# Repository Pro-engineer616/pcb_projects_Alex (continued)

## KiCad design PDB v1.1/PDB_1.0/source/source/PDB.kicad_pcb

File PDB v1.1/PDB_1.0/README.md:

PDB (Power delivery board Rev. 1.0)

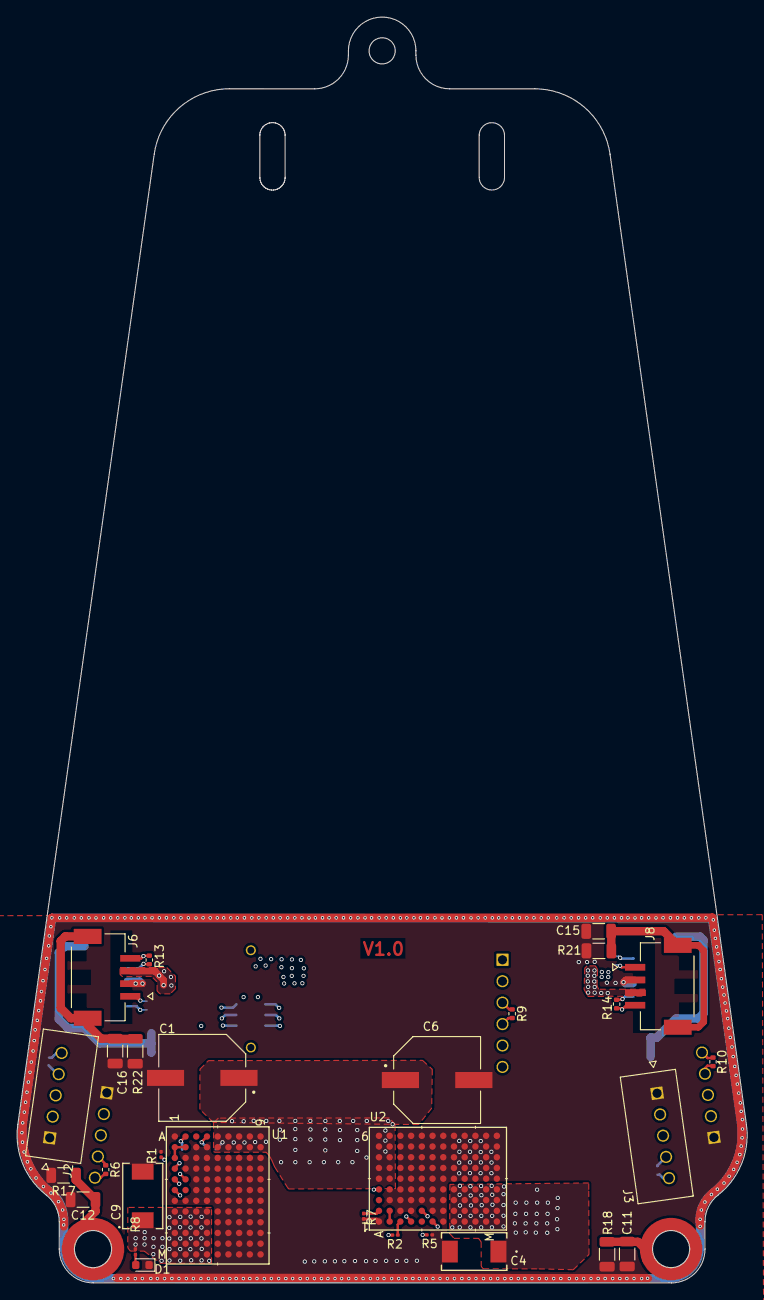
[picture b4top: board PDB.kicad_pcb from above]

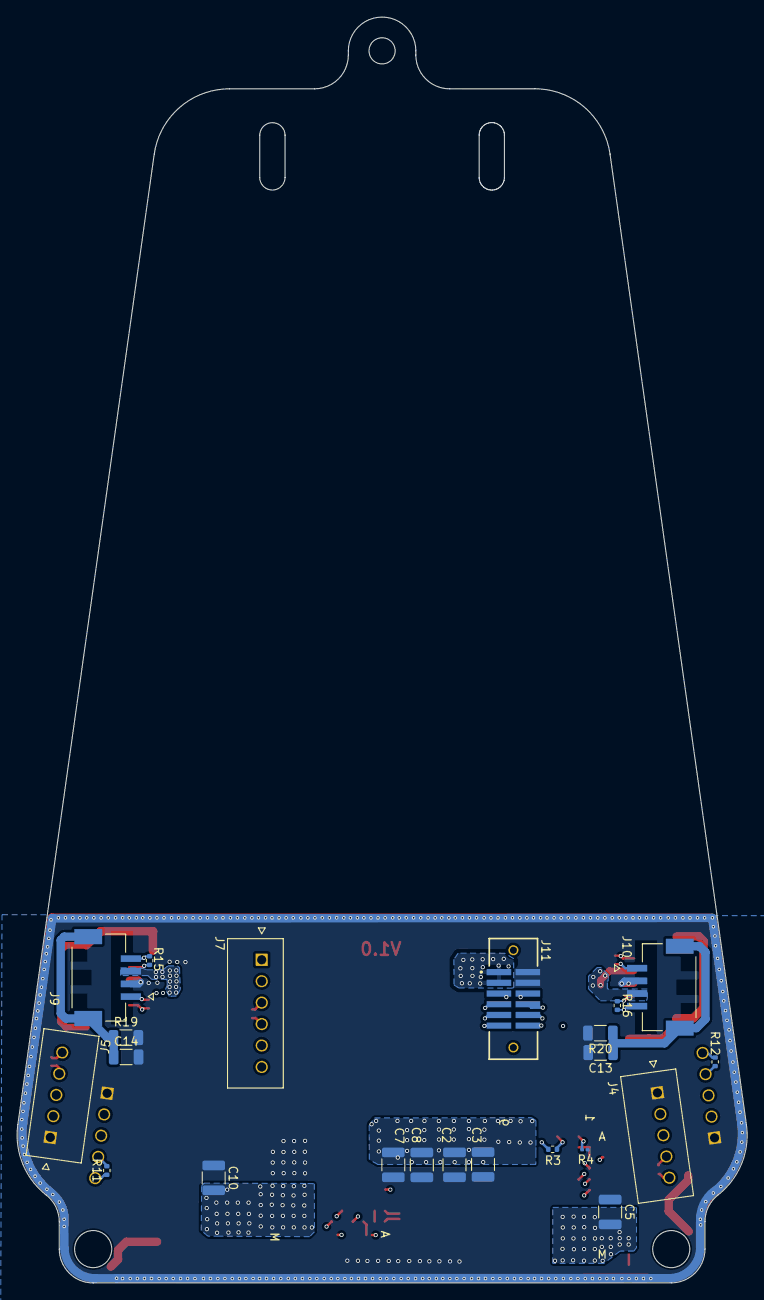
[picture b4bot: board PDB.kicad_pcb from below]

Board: 4 copper layers, 86.5 x 150.0 mm, 53 parts (22 on the bottom side), 29 nets.

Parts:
C1, C6: 15uf; CAP_100SXV15MX
C2, C3, C7, C8: 10u; C_1210_3225Metric
C4, C9: 150uF; CAP_TRM-E-2917_AVX-L
C5, C10: 100uF; C_1210_3225Metric
C11, C12, C13, C14, C15, C16: 470pF; C_1206_3216Metric
D1: NCD0603C1; LED_0603_1608Metric
J2, J3, J4, J5: 1719710105; MOLEX_1719710105
J6, J8, J9, J10: 2132250430; MOLEX_2132250430
J7: 1719710106; MOLEX_1719710106
J11: TFM-106-02-L-D-WT; SAMTEC_TFM-106-02-L-D-WT
MP1, MP2: WA-SMSI_9774XXX360; WA-SMSI_9774120360
R1, R5: 124k; R_0201_0603Metric
R2: 100k; R_0201_0603Metric
R3: 374k; R_0402_1005Metric
R4, R7: 2.87k; R_0201_0603Metric
R6, R9, R10, R11, R12, R13, R14, R15, R16: 120R; R_0402_1005Metric
R8: 10k; R_0201_0603Metric
R17, R18, R19, R20, R21, R22: 2M; C_1206_3216Metric
U1, U2: LTM8064IY#PBF; BGA108_16X11P9_ADI

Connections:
+8V: C4.1, C5.2, C9.1, C10.2, J2.2, J3.2, J4.2, J5.2, J7.5, R8.2, U1.H1 (VOUT), U1.H2 (VOUT), U1.H3 (VOUT), U1.H4 (VOUT), U1.J1 (VOUT), U1.J2 (VOUT), U1.J3 (VOUT), U1.J4 (VOUT), U1.K1 (VOUT), U1.K2 (VOUT), U1.K3 (VOUT), U1.K4 (VOUT), U1.L1 (VOUT), U1.L2 (VOUT), U1.L3 (VOUT), U1.L4 (VOUT), U1.M1 (VOUT), U1.M2 (VOUT), U1.M3 (VOUT), U1.M4 (VOUT), U2.H1 (VOUT), U2.H2 (VOUT), U2.H3 (VOUT), U2.H4 (VOUT), U2.J1 (VOUT), U2.J2 (VOUT), U2.J3 (VOUT), U2.J4 (VOUT), U2.K1 (VOUT), U2.K2 (VOUT), U2.K3 (VOUT), U2.K4 (VOUT), U2.L1 (VOUT), U2.L2 (VOUT), U2.L3 (VOUT), U2.L4 (VOUT), U2.M1 (VOUT), U2.M2 (VOUT), U2.M3 (VOUT), U2.M4 (VOUT)
/power/IOUTMON: R2.1, U2.C1 (CTRL1)
/power/PWR_RUN: R3.1, U1.A4 (RUN), U2.A4 (RUN)
/power/PWR_SS: U1.D1 (SS), U2.D1 (SS)
/power/SYNC: U1.F1 (SYNC), U2.F1 (SYNC)
CAN H1: J2.5, J3.5, J4.5, J5.5, J6.1, J7.3, J8.1, J9.1, J10.1, J11.05, R6.1, R9.1, R10.1, R11.1, R12.1, R13.1, R14.1, R15.1, R16.1
CAN L1: J2.4, J3.4, J4.4, J5.4, J6.4, J7.4, J8.4, J9.4, J10.4, J11.06, R6.2, R9.2, R10.2, R11.2, R12.2, R13.2, R14.2, R15.2, R16.2
Detach: J7.2, J11.07
GND: C1.2, C2.2, C3.2, C4.2, C5.1, C6.2, C7.2, C8.2, C9.2, C10.1, C11.2, C12.2, C13.2, C14.2, C15.2, C16.2, D1.1 (K), J2.1, J3.1, J4.1, J5.1, J6.2, J8.2, J9.2, J10.2, J11.02, J11.04, R1.1, R4.2, R5.1, R7.2, R17.2, R18.2, R19.2, R20.2, R21.2, R22.2, U1.A1 (GND), U1.B3 (GND), U1.B4 (GND), U1.C2 (GND), U1.C3 (GND), U1.C4 (GND), U1.C5 (GND), U1.C6 (GND), U1.C7 (GND), U1.C8 (GND), U1.C9 (GND), U1.D2 (GND), U1.D3 (GND), U1.D4 (GND), U1.D5 (GND), U1.D6 (GND), U1.D7 (GND), U1.D8 (GND), U1.D9 (GND), U1.E3 (GND), U1.E4 (GND), U1.E5 (GND), U1.E6 (GND), U1.E7 (GND), U1.E8 (GND), U1.E9 (GND), U1.F3 (GND), U1.F4 (GND), U1.F5 (GND), U1.F6 (GND), U1.F7 (GND), U1.F8 (GND), U1.F9 (GND), U1.G1 (GND), U1.G2 (GND), U1.G3 (GND), U1.G4 (GND), U1.G5 (GND), U1.G6 (GND), U1.G7 (GND), U1.G8 (GND), U1.G9 (GND), U1.H5 (GND), U1.H6 (GND), U1.H7 (GND), U1.H8 (GND), U1.H9 (GND), U1.J5 (GND), U1.J6 (GND), U1.J7 (GND), U1.J8 (GND), U1.J9 (GND), U1.K5 (GND), U1.K6 (GND), U1.K7 (GND), U1.K8 (GND), U1.K9 (GND), U1.L5 (GND), U1.L6 (GND), U1.L7 (GND), U1.L8 (GND), U1.L9 (GND), U1.M5 (GND), U1.M6 (GND), U1.M7 (GND), U1.M8 (GND), U1.M9 (GND), U2.A1 (GND), U2.B3 (GND), U2.B4 (GND), U2.C2 (GND), U2.C3 (GND), U2.C4 (GND), U2.C5 (GND), U2.C6 (GND), U2.C7 (GND), U2.C8 (GND), U2.C9 (GND), U2.D2 (GND), U2.D3 (GND), U2.D4 (GND), U2.D5 (GND), U2.D6 (GND), U2.D7 (GND), U2.D8 (GND), U2.D9 (GND), U2.E3 (GND), U2.E4 (GND), U2.E5 (GND), U2.E6 (GND), U2.E7 (GND), U2.E8 (GND), U2.E9 (GND), U2.F2 (MODE), U2.F3 (GND), U2.F4 (GND), U2.F5 (GND), U2.F6 (GND), U2.F7 (GND), U2.F8 (GND), U2.F9 (GND), U2.G1 (GND), U2.G2 (GND), U2.G3 (GND), U2.G4 (GND), U2.G5 (GND), U2.G6 (GND), U2.G7 (GND), U2.G8 (GND), U2.G9 (GND), U2.H5 (GND), U2.H6 (GND), U2.H7 (GND), U2.H8 (GND), U2.H9 (GND), U2.J5 (GND), U2.J6 (GND), U2.J7 (GND), U2.J8 (GND), U2.J9 (GND), U2.K5 (GND), U2.K6 (GND), U2.K7 (GND), U2.K8 (GND), U2.K9 (GND), U2.L5 (GND), U2.L6 (GND), U2.L7 (GND), U2.L8 (GND), U2.L9 (GND), U2.M5 (GND), U2.M6 (GND), U2.M7 (GND), U2.M8 (GND), U2.M9 (GND)
GND_FUSE: J7.1, J11.08
unnamed: C11.1, MP2.1, R18.1
unnamed: C12.1, MP1.1, R17.1
unnamed: D1.2 (A), R8.1
unnamed: C16.1, J6.S1 (SHIELD1), J6.S2 (SHIELD2), R22.1
unnamed: C15.1, J8.S1 (SHIELD1), J8.S2 (SHIELD2), R21.1
unnamed: C14.1, J9.S1 (SHIELD1), J9.S2 (SHIELD2), R19.1
unnamed: C13.1, J10.S1 (SHIELD1), J10.S2 (SHIELD2), R20.1
unnamed: U1.B1 (CTRL2), U1.B2 (VREF), U1.C1 (CTRL1)
unnamed: R4.1, U1.A2 (FB)
unnamed: R2.2, U1.E1 (IOUTMON)
unnamed: R1.2, U1.E2 (RT)
unnamed: U2.B1 (CTRL2), U2.B2 (VREF)
unnamed: R7.1, U2.A2 (FB)
unnamed: R5.2, U2.E2 (RT)
PWM1: J5.3, J11.09
PWM2: J4.3, J11.10
PWM3: J3.3, J11.11
PWM4: J2.3, J11.12
VBAT: C1.1, C2.1, C3.1, C6.1, C7.1, C8.1, J6.3, J8.3, J9.3, J10.3, J11.01, J11.03, R3.2, U1.A5 (VIN), U1.A6 (VIN), U1.A7 (VIN), U1.A8 (VIN), U1.A9 (VIN), U1.B5 (VIN), U1.B6 (VIN), U1.B7 (VIN), U1.B8 (VIN), U1.B9 (VIN), U2.A5 (VIN), U2.A6 (VIN), U2.A7 (VIN), U2.A8 (VIN), U2.A9 (VIN), U2.B5 (VIN), U2.B6 (VIN), U2.B7 (VIN), U2.B8 (VIN), U2.B9 (VIN)

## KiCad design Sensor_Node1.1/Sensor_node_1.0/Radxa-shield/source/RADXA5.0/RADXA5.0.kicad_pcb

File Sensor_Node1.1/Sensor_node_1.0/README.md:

View this project on [CADLAB.io](https://cadlab.io/project/28262). 

# sensor_node
Airspeed, Compass and UART as CAN sensor

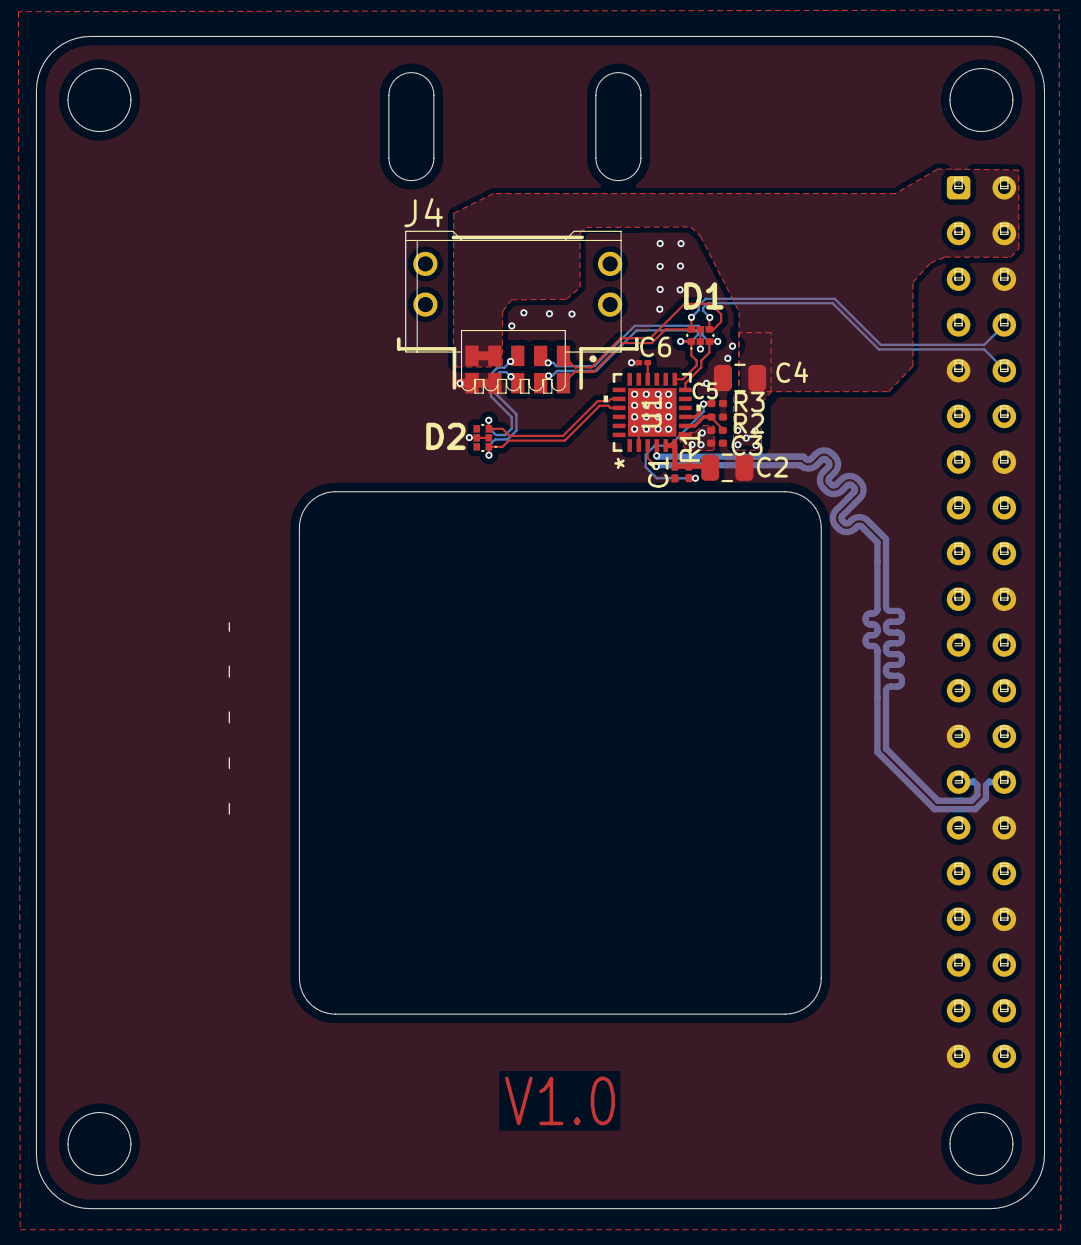
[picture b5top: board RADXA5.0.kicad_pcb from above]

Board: 2 copper layers, 56.0 x 65.1 mm, 14 parts (1 on the bottom side), 14 nets.

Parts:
C1, C3, C5: 100n; C_0201_0603Metric
C2, C4: 10u; C_0805_2012Metric
C6: 4.7u; C_01005_0402Metric
D1, D2: PESD3V3L4UF,115; PESD3V3L5UF115
J1: Conn_02x10_Odd_Even; Samtec_HLE-120-02-xx-DV-TE_2x20_P2.54mm_Horizontal
J4: TFM-105-02-L-DH; SAMTEC_TFM-105-02-L-DH
R1: 4.3k; R_0201_0603Metric
R2: 24k; R_0201_0603Metric
R3: 47k; R_0201_0603Metric
U1: CP2105-F01-GM; QFN24_4X4_SIL-L

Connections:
5VSYS: C3.1, C4.1, J1.2, J1.4, J4.07, J4.09, R2.1, U1.7 (REGIN)
GND: C1.2, C2.2, C3.2, C4.2, C5.2, C6.2, D1.2 (common_anode_1), D1.5 (common_anode_2), D2.2 (common_anode_1), D2.5 (common_anode_2), J1.6, J1.9, J1.14, J1.20, J1.25, J1.30, J1.34, J1.39, J4.08, J4.10, R3.1, U1.2 (GND), U1.25 (EPAD)
unnamed: C5.1, R1.2, U1.9 (*RST)
unnamed: C6.1, U1.16 (NC/DCD_ECI/VPP)
unnamed: R2.2, R3.2, U1.8 (VBUS)
UART1_RX: D1.4 (cathode_(diode_3)), J1.10, J4.01
UART1_TX: D1.6 (cathode_(diode_4)), J1.8, J4.02
UART2_RX: D1.3 (cathode_(diode_2)), J4.03, U1.12 (RXD_ECI)
UART2_TX: D1.1 (cathode_(diode_1)), J4.04, U1.13 (TXD_ECI)
UART3_RX: D2.3 (cathode_(diode_2)), J4.05, U1.20 (RXD_SCI)
UART3_TX: D2.1 (cathode_(diode_1)), J4.06, U1.21 (TXD_SCI)
USB_N: J1.27, U1.4 (D-)
USB_P: J1.28, U1.3 (D+)
VDD: C1.1, C2.1, R1.1, U1.5 (VIO), U1.6 (VDD)

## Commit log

2024-08-19 initial
2024-08-19 updated folder structure
2024-08-19 Add Source and production files
    Add Source and production files
2024-08-19 Add PDB, sensor_node projects
    Add PDB, sensor_node projects
2024-08-21 Add the calculation for UART_HUB and USB_HUB
    Add the calculation for UART_HUB and USB_HUB
2024-08-29 Add infrastructure project
    Add infrastructure project
2024-09-03 Update VBAT net
    connection VBAT net to +5V
2024-09-03 Add Radxa shield rev 1.2
2024-09-03 Add PDB1.1
2024-09-09 Add production data files
    PDB1.2, SensornodeV1.2, infrastructure
2024-09-09 Add productiondata
2024-09-12 Update the mosfet with sot-23 package in PDB1.2 project
    Update the mosfet with sot-23 package in PDB1.2 project
2024-09-18 Add PDB1.4
    Add PDB1.4 included all source files.
2024-09-18 Add PDB1.4
2024-09-18 Add BOM file
    Add BOM file
2024-09-18 Add Version text
    Add Version text
2024-09-18 Add version
2024-09-18 Add remove filling
    Add remove filling
2024-09-18 Add PCB specification of PDB v1.4
    Add PCB specification of PDB v1.4
2024-09-19 Update all projects
    add the items as following
    - PCB specifications
    - production files of PCBWay, JLCPCB
2024-09-19 Add zip files
2024-09-19 Add sensornode_CPL
2024-09-19 Add BOM of PDB v1.4
2024-09-19 add missed files
2024-09-19 test
2024-09-19 Add board Name
2024-09-19 rename
